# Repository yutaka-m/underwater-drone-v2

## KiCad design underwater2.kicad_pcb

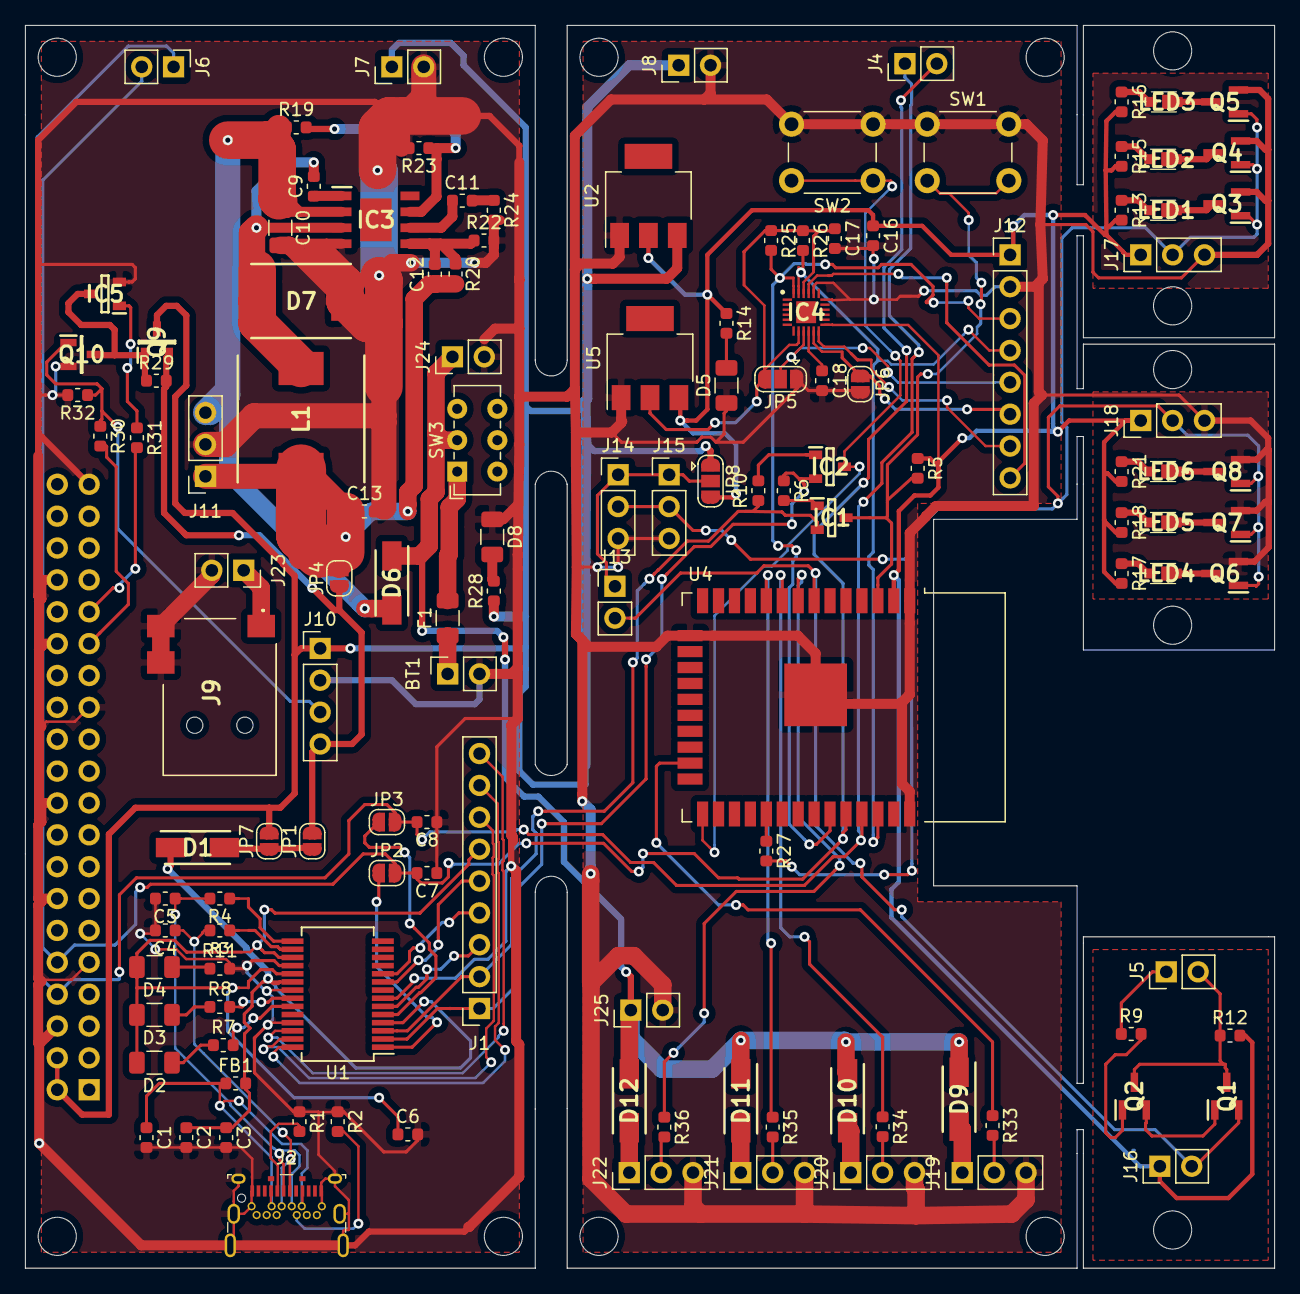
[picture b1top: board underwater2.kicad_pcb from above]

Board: 2 copper layers, 99.6 x 99.1 mm, 129 parts (1 on the bottom side), 94 nets.

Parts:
BT1: BATT in; PinSocket_1x02_P2.54mm_Vertical
C1: 10nF; C_0603_1608Metric
C2, C6: 100nF; C_0603_1608Metric
C3: 4.7μF; C_0603_1608Metric
C4, C5: if necessary; C_0603_1608Metric
C7, C8: 0μF; C_0603_1608Metric
C9: 10nF/25V; C_0603_1608Metric
C10: 10µF/50V; C_1206_3216Metric
C11: 4.7nF/25V; C_0603_1608Metric
C12: 1nF/16V; C_0603_1608Metric
C13: 22µF/10V; C_0603_1608Metric
C16, C17, C18: 0.1μF; C_0603_1608Metric
D1, D6, D9, D10, D11, D12: 34/40V 3A; DIOM5226X240N
D2: TX; C_1206_3216Metric
D3: RX; C_1206_3216Metric
D4: Pwr USB; C_1206_3216Metric
D5: Pwr 3.3V; C_1206_3216Metric
D7: 40V/3A; DIONM7959X282N
D8: Pwr 5V; C_1206_3216Metric
F1: fuse 10A; R_1206_3216Metric
FB1: Ferrite_Bead_Small; C_0603_1608Metric
IC1, IC2, IC5: KST10MTF; SOT95P240X120-3N
IC3: ACT4070BYH-T; SOIC127P600X170-9N
IC4: ICM-20948; QFN40P300X300X105-25N-D
J1: test con; PinSocket_1x09_P2.54mm_Vertical
J2: USB_C_Receptacle_USB2.0; USB-C_Female_E8124-015-01
J3: Raspberry_Pi_2_3; PinSocket_2x20_P2.54mm_Vertical
J4: serial; PinHeader_1x02_P2.54mm_Vertical
J5: Water; PinHeader_1x02_P2.54mm_Vertical
J6: serial2; PinHeader_1x02_P2.54mm_Vertical
J7, J8: 5v pow; PinHeader_1x02_P2.54mm_Vertical
J9: PJ1-021-SMT-TR; PJ1021SMTTR
J10: momentary switch; PinHeader_1x04_P2.54mm_Vertical
J11: ext regurator; PinSocket_1x03_P2.54mm_Vertical
J12: ICM20948 out; PinHeader_1x08_P2.54mm_Vertical
J13: Water Sence; PinHeader_1x02_P2.54mm_Vertical
J14: LED Left; PinHeader_1x03_P2.54mm_Vertical
J15: LED right; PinHeader_1x03_P2.54mm_Vertical
J16: Water con; PinHeader_1x02_P2.54mm_Vertical
J17: LED left con; PinHeader_1x03_P2.54mm_Vertical
J18: LED right con; PinHeader_1x03_P2.54mm_Vertical
J19: BLMOTOR_B2; PinHeader_1x03_P2.54mm_Vertical
J20: BLMOTOR_B1; PinHeader_1x03_P2.54mm_Vertical
J21: BLMOTOR_A2; PinHeader_1x03_P2.54mm_Vertical
J22: BLMOTOR_A1; PinHeader_1x03_P2.54mm_Vertical
J23: BATT Chrg; PinSocket_1x02_P2.54mm_Vertical
J24, J25: BT pow; PinHeader_1x02_P2.54mm_Vertical
JP1: J usbpower; SolderJumper-2_P1.3mm_Open_RoundedPad1.0x1.5mm
JP2: tx rx; SolderJumper-2_P1.3mm_Open_RoundedPad1.0x1.5mm
JP3: rx tx; SolderJumper-2_P1.3mm_Open_RoundedPad1.0x1.5mm
JP4: BATT power; SolderJumper-2_P1.3mm_Open_RoundedPad1.0x1.5mm
JP5, JP8: SolderJumper_3_Open; SolderJumper-3_P1.3mm_Open_RoundedPad1.0x1.5mm
JP6: SolderJumper_2_Open; SolderJumper-2_P1.3mm_Open_RoundedPad1.0x1.5mm
JP7: charge; SolderJumper-2_P1.3mm_Open_RoundedPad1.0x1.5mm
L1: 15µH4A; B952ASH100MP3
LED1, LED2, LED3, LED4, LED5, LED6: MP-2016-1100-65-70; MP201611006570
Q1, Q2, Q3, Q4, Q5, Q6, Q7, Q8: 2SC2712-Y,LF; SOT95P260X140-3N
Q9: DMP3099L-7; SOT96P240X120-3N
Q10: IRLML6344TRPBF; SOT95P237X112-3N
R1, R2: 5.1k; C_0603_1608Metric
R3, R4: 27; C_0603_1608Metric
R5, R6, R10: 10k; C_0603_1608Metric
R7, R8, R11, R14, R28: 270; C_0603_1608Metric
R9, R12, R25, R26, R31: 1k; C_0603_1608Metric
R13, R15, R16, R17, R18, R21: 67; C_0603_1608Metric
R19: 1M; C_0603_1608Metric
R20: 51k; C_0603_1608Metric
R22: 9.76k; C_0603_1608Metric
R23: 330k; C_0603_1608Metric
R24: 12k; C_0603_1608Metric
R27, R33, R34, R35, R36: 100; C_0603_1608Metric
R29, R32: 100k; C_0603_1608Metric
R30: 39k; C_0603_1608Metric
SW1, SW2: SW_Push_Dual; SW_PUSH_6mm
SW3: SW_DIP_x01; SW_E-Switch_EG1271_DPDT
U1: FT232RL; SSOP-28_5.3x10.2mm_P0.65mm
U2: LM1117-3.3; SOT-223
U4: ESP32-WROOM-32
U5: LM1117-1.8; SOT-223

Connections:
+3V3: C16.1, IC4.13, J12.1, J16.1, J17.1, J18.1, JP8.3, R5.1, R12.2, R13.2, R14.1, R15.2, R16.2, R17.2, R18.2, R21.2, U2.2, U4.2, U5.3
+5V: J3.2, J3.4, J7.1, J8.1, J10.1, JP7.2, JP8.1, Q9.3, R28.1, U2.3
+BATT: D6.1, D9.1, D10.1, D11.1, D12.1, J24.1, J25.1, SW3.2
+VSW: J10.4, JP1.2, JP4.1, Q9.2, R29.2
-BATT: BT1.2, C1.2, C2.2, C3.2, C4.2, C5.2, C6.2, C7.1, C8.1, C10.2, C13.2, C16.2, C17.2, C18.2, D5.1, D7.1, D8.1, IC3.4, IC4.18, IC4.20, IC5.2, J2.A1, J2.A12, J2.B1, J2.B12, J2.SH, J3.6, J3.9, J3.14, J3.20, J3.25, J3.30, J3.34, J3.39, J7.2, J8.2, J9.2, J9.3, J10.2, J11.2, J12.2, J14.3, J15.3, J17.3, J18.3, J19.3, J20.3, J21.3, J22.3, J23.2, J24.2, J25.2, JP5.1, JP6.2, Q3.2, Q4.2, Q5.2, Q6.2, Q7.2, Q8.2, Q10.2, R1.1, R2.1, R11.2, R22.2, R23.2, R24.2, R32.2, SW1.1, SW2.2, U1.7, U1.18, U1.21, U1.25, U2.1, U4.1, U4.15, U4.38, U4.39, U5.1
ESP_EN: IC1.3, R5.2, SW1.2, U4.3
GPIO5: J3.29, R30.2
GPIO6: J3.31, R31.2
IO0: IC2.3, SW2.1, U4.25
IO15: R33.1, U4.23
IO25: R35.1, U4.10
IO32: R36.1, U4.8
IO33: R34.1, U4.9
LED_SW: J14.2, J15.2, J17.2, J18.2, Q3.1, Q4.1, Q5.1, Q6.1, Q7.1, Q8.1, R27.2
unnamed: BT1.1, F1.1
unnamed: C1.1, FB1.1, J2.A4, J2.A9, J2.B4, J2.B9
unnamed: C2.1, C3.1, D1.1, FB1.2, U1.4, U1.20
unnamed: C4.1, J2.A7, J2.B7, R3.2
unnamed: C5.1, J2.A6, J2.B6, R4.2
unnamed: C9.1, IC3.1
unnamed: C9.2, D7.2, IC3.3, L1.2
unnamed: C10.1, D6.2, IC3.2, J11.3, R19.1
unnamed: C11.1, IC3.6
unnamed: C11.2, R24.1
unnamed: C12.1, C13.1, J11.1, JP4.2, L1.1, R20.1
unnamed: C12.2, IC3.5, R20.2, R22.1
unnamed: C17.1, IC4.8, IC4.22, JP5.3, R25.1, R26.1, U5.2
unnamed: C18.1, IC4.10
unnamed: D1.2, JP1.1, JP7.1
unnamed: D2.1, R7.1
unnamed: D3.1, R8.1
unnamed: D4.1, R11.1
unnamed: D5.2, R14.2
unnamed: D8.2, R28.2
unnamed: D9.2, J19.1
unnamed: D10.2, J20.1
unnamed: D11.2, J21.1
unnamed: D12.2, J22.1
unnamed: F1.2, SW3.1
unnamed: IC1.1, R6.2
unnamed: IC2.1, R10.2
unnamed: IC3.7, R19.2, R23.1
unnamed: IC4.9, J12.5, JP5.2
unnamed: IC4.11, J12.6, JP6.1
unnamed: IC4.12, J12.7
unnamed: IC4.21, J12.8
unnamed: IC5.1, R31.1
unnamed: IC5.3, Q9.1, Q10.3, R29.1
unnamed: J2.A5, R1.2
unnamed: J2.B5, R2.2
unnamed: J5.1, R9.1
unnamed: J5.2, Q1.3, Q2.3, R12.1
unnamed: J10.3, Q10.1, R30.1, R32.1
unnamed: J13.1, J14.1, J15.1, JP8.2
unnamed: J19.2, R33.2
unnamed: J20.2, R34.2
unnamed: J21.2, R35.2
unnamed: J22.2, R36.2
unnamed: J9.1, J23.1
unnamed: LED1.1, LED1.2, Q3.3
unnamed: LED1.3, LED1.4, R13.1
unnamed: LED2.1, LED2.2, Q4.3
unnamed: LED2.3, LED2.4, R15.1
unnamed: LED3.1, LED3.2, Q5.3
unnamed: LED3.3, LED3.4, R16.1
unnamed: LED4.1, LED4.2, Q6.3
unnamed: LED4.3, LED4.4, R17.1
unnamed: LED5.1, LED5.2, Q7.3
unnamed: LED5.3, LED5.4, R18.1
unnamed: LED6.1, LED6.2, Q8.3
unnamed: LED6.3, LED6.4, R21.1
unnamed: Q1.1, Q2.2
unnamed: Q2.1, R9.2
unnamed: R7.2, U1.23
unnamed: R8.2, U1.22
unnamed: R27.1, U4.29
RXD0: C7.2, J3.10, J4.2, J6.2, JP2.2, U4.34
SCL: IC4.23, J12.4, R26.2, U4.36
SDA: IC4.24, J12.3, R25.2, U4.33
TXD0: C8.2, J3.8, J4.1, J6.1, JP3.2, U4.35
USBD+: R4.1, U1.15
USBD-: R3.1, U1.16
USB_DCD: J1.4, U1.10
USB_DCR: J1.5, U1.9
USB_DTR: IC2.2, J1.1, R6.1, U1.2
USB_NRESET: C6.1, D2.2, D3.2, D4.2, J1.6, U1.17, U1.19
USB_OSCI: J1.7, U1.27
USB_OSCO: J1.8, U1.28
USB_RI: J1.3, U1.6
USB_RTS: IC1.2, J1.2, R10.1, U1.3
USB_RXD: JP3.1, U1.5
USB_TEST: J1.9, U1.26
USB_TXD: JP2.1, U1.1
WATER: J13.2, J16.2, Q1.2, U4.7

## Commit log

2020-08-30 Modify milestone 2020724
2020-10-13 Add broken charger.
2020-10-19 Modified drive ESC and external switch.
